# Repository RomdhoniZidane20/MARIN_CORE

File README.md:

# MARIN Core
ICHIRO Controller Manager Board for Dynamixel
## Features

* RS485/TTL on 4 Buses
* BNO055 IMU Sensor With Absolute Orientation
* Hot Swap switching System for Mini PC (Intel NUC 10th)
* Motor Voltage Power Switch System

## Include Hardware and Software setup for dxl_board

Documentations for [FT4232_dxl](https://github.com/RomdhoniZidane20/ichiro_dxl_board/tree/main/firmware/FT4232)

Documentations for [MARIN_CORE](https://github.com/RomdhoniZidane20/ichiro_dxl_board/tree/main/firmware/Marin_Core_Firmware)

Documentations for [Loadcel_dxl](https://github.com/RomdhoniZidane20/ichiro_dxl_board/tree/main/firmware/Loadcell)

Documentations for [Interface_dxl](https://github.com/RomdhoniZidane20/ichiro_dxl_board/tree/main/firmware/Interface)

## License 
The FT4232 and ADM3078E eagle library of this repository based on 
"SUSTAINA-OP" by [Masato Kubotera](https://github.com/MasatoKubotera) is licensed under [ CC BY-NC-SA 4.0](https://creativecommons.org/licenses/by-nc-sa/4.0/).

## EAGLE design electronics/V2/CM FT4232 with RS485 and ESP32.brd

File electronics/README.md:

# License 
The FT4232 and ADM3078E eagle library of this repository based on  
"SUSTAINA-OP" by [Masato Kubotera](https://github.com/MasatoKubotera) is licensed under [ CC BY-NC-SA 4.0](https://creativecommons.org/licenses/by-nc-sa/4.0/).

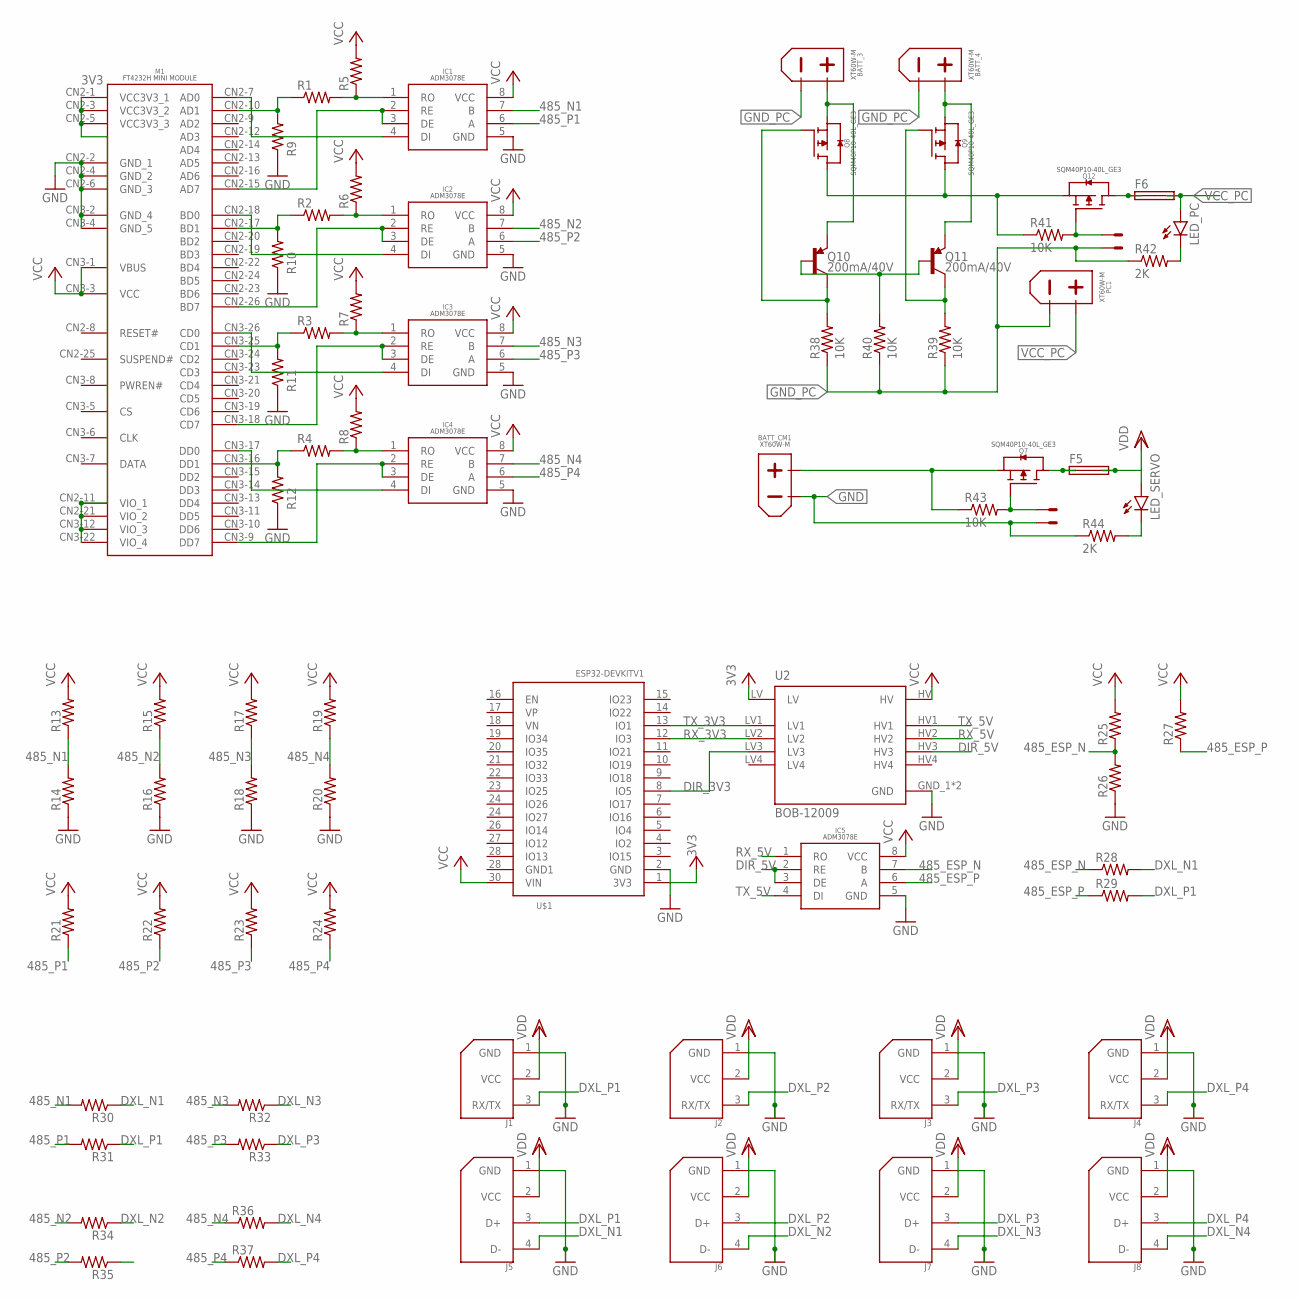
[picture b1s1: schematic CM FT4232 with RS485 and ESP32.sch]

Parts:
BATT_3, BATT_4: XT60PW-M
BATT_CM1: XT60PW-M
F5, F6: SHK20L
IC1, IC2, IC3, IC4, IC5: ADM3078E
J1, J2, J3, J4: 22-03-5035; 5267-3
J5, J6, J7, J8: 22-03-5045; 5267-4
LED_PC: LEDCHIPLED_0805; CHIPLED_0805
LED_SERVO: LEDCHIPLED_0805; CHIPLED_0805
M1: FT4232H_MINI_MODULE
PC1: XT60PW-M
Q7, Q8, Q9, Q12: SQM40P10-40L_GE3; TO-252-3
Q10, Q11: 200mA/40V; SOT23-3
R1, R2, R3, R4, R5, R6, R7, R8, R9, R10, R11, R12, R13, R14, R15, R16, R17, R18, R19, R20, R21, R22, R23, R24, R25, R26, R27, R28, R29, R30, R31, R32, R33, R34, R35, R36, R37: 0805
R38, R39, R40, R41, R43: 10K; M0805
R42, R44: 2K; M0805
U2: BOB-12009; CONV_BOB-12009
U$1: ESP32DEVKITV1; ESP32-DEVKITV1
X7, X8: 22-23-2021

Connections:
3V3: M1.CN2-1 (VCC3V3_1), M1.CN2-3 (VCC3V3_2), M1.CN2-5 (VCC3V3_3), M1.CN2-11 (VIO_1), M1.CN2-21 (VIO_2), M1.CN3-12 (VIO_3), M1.CN3-22 (VIO_4), U2.LV, U$1.1 (3V3)
485_ESP_N: IC5.7 (B), R25.1, R26.2, R28.1
485_ESP_P: IC5.6 (A), R27.1, R29.1
485_N1: IC1.7 (B), R13.1, R14.2, R30.2
485_N2: IC2.7 (B), R15.1, R16.2, R34.2
485_N3: IC3.7 (B), R17.1, R18.2, R32.2
485_N4: IC4.7 (B), R19.1, R20.2, R36.1
485_P1: IC1.6 (A), R21.1, R31.2
485_P2: IC2.6 (A), R22.1, R35.2
485_P3: IC3.6 (A), R23.1, R33.2
485_P4: IC4.6 (A), R24.1, R37.1
+2: BATT_CM1.+, Q7.3 (S), R43.1
+3: Q8.4 (D), Q9.4 (D), Q12.3 (S), R41.1
BLUE_LED: U$1.26 (IO14)
DI1: IC1.4 (DI), M1.CN2-7 (AD0)
DIR_3V3: U2.LV3, U$1.8 (IO5)
DIR_5V: IC5.2 (RE), IC5.3 (DE), U2.HV3
DRAIN2: F5.1A, F5.1B, Q7.4 (D)
DRAIN3: F6.1A, F6.1B, Q12.4 (D)
DXL_ENABLE: U$1.21 (IO32)
DXL_N1: J5.4 (D-), R28.2, R30.1
DXL_N2: J6.4 (D-), R34.1
DXL_N3: J7.4 (D-), R32.1
DXL_N4: J8.4 (D-), R36.2
DXL_P1: J1.3 (RX/TX), J5.3 (D+), R29.2, R31.1
DXL_P2: J2.3 (RX/TX), J6.3 (D+), R35.1
DXL_P3: J3.3 (RX/TX), J7.3 (D+), R33.1
DXL_P4: J4.3 (RX/TX), J8.3 (D+), R37.2
GND: BATT_CM1.1 (-), BATT_CM1.2 (-), BATT_CM1.-, IC1.5 (GND), IC2.5 (GND), IC3.5 (GND), IC4.5 (GND), IC5.5 (GND), J1.1 (GND), J2.1 (GND), J3.1 (GND), J4.1 (GND), J5.1 (GND), J6.1 (GND), J7.1 (GND), J8.1 (GND), M1.CN2-2 (GND_1), M1.CN2-4 (GND_2), M1.CN2-6 (GND_3), M1.CN3-2 (GND_4), M1.CN3-4 (GND_5), R9.1, R10.1, R11.1, R12.1, R14.1, R16.1, R18.1, R20.1, R26.1, R44.1, U2.GND_1 (GND), U2.GND_2 (GND), U$1.2 (GND), X7.2
GND_PC: BATT_3.1 (-), BATT_3.2 (-), BATT_3.-, BATT_4.1 (-), BATT_4.2 (-), BATT_4.-, PC1.1 (-), PC1.2 (-), PC1.-, R38.1, R39.1, R40.1, R42.1, X8.2
GREE_LED: U$1.28 (IO13)
unnamed: IC2.2 (RE), IC2.3 (DE), M1.CN2-26 (BD7)
unnamed: IC3.2 (RE), IC3.3 (DE), M1.CN3-18 (CD7)
unnamed: IC4.2 (RE), IC4.3 (DE), M1.CN3-9 (DD7)
unnamed: M1.CN2-10 (AD1), R1.1, R9.2
unnamed: M1.CN2-17 (BD1), R2.1, R10.2
unnamed: IC2.1 (RO), R2.2, R6.1
unnamed: IC3.1 (RO), R3.2, R7.1
unnamed: M1.CN3-25 (CD1), R3.1, R11.2
unnamed: M1.CN3-16 (DD1), R4.1, R12.2
unnamed: IC4.1 (RO), R4.2, R8.1
unnamed: IC2.4 (DI), M1.CN2-18 (BD0)
unnamed: IC3.4 (DI), M1.CN3-26 (CD0)
unnamed: IC4.4 (DI), M1.CN3-17 (DD0)
unnamed: BATT_3.+, Q8.3 (S), Q10.2 (E)
unnamed: BATT_4.+, Q9.3 (S), Q11.2 (E)
unnamed: Q8.1 (G), Q10.3 (C), R38.2
unnamed: Q9.1 (G), Q11.3 (C), R39.2
unnamed: Q10.1 (B), Q11.1 (B), R40.2
unnamed: Q12.1 (G), R41.2, X8.1
unnamed: Q7.1 (G), R43.2, X7.1
unnamed: LED_PC.C, R42.2
unnamed: LED_SERVO.C, R44.2
RE1: IC1.2 (RE), IC1.3 (DE), M1.CN2-15 (AD7)
RED_LED: U$1.27 (IO12)
RO1: IC1.1 (RO), R1.2, R5.1
RX_3V3: U2.LV2, U$1.12 (IO3)
RX_5V: IC5.1 (RO), U2.HV2
SCL: U$1.14 (IO22)
SDA: U$1.11 (IO21)
SW_START: U$1.19 (IO34)
SW_STOP: U$1.20 (IO35)
TX_3V3: U2.LV1, U$1.13 (IO1)
TX_5V: IC5.4 (DI), U2.HV1
VCC: IC1.8 (VCC), IC2.8 (VCC), IC3.8 (VCC), IC4.8 (VCC), IC5.8 (VCC), M1.CN3-1 (VBUS), M1.CN3-3 (VCC), R5.2, R6.2, R7.2, R8.2, R13.2, R15.2, R17.2, R19.2, R21.2, R22.2, R23.2, R24.2, R25.2, R27.2, U2.HV, U$1.30 (VIN)
VCC_PC: F6.2A, F6.2B, LED_PC.A, PC1.+
VDD: F5.2A, F5.2B, J1.2 (VCC), J2.2 (VCC), J3.2 (VCC), J4.2 (VCC), J5.2 (VCC), J6.2 (VCC), J7.2 (VCC), J8.2 (VCC), LED_SERVO.A

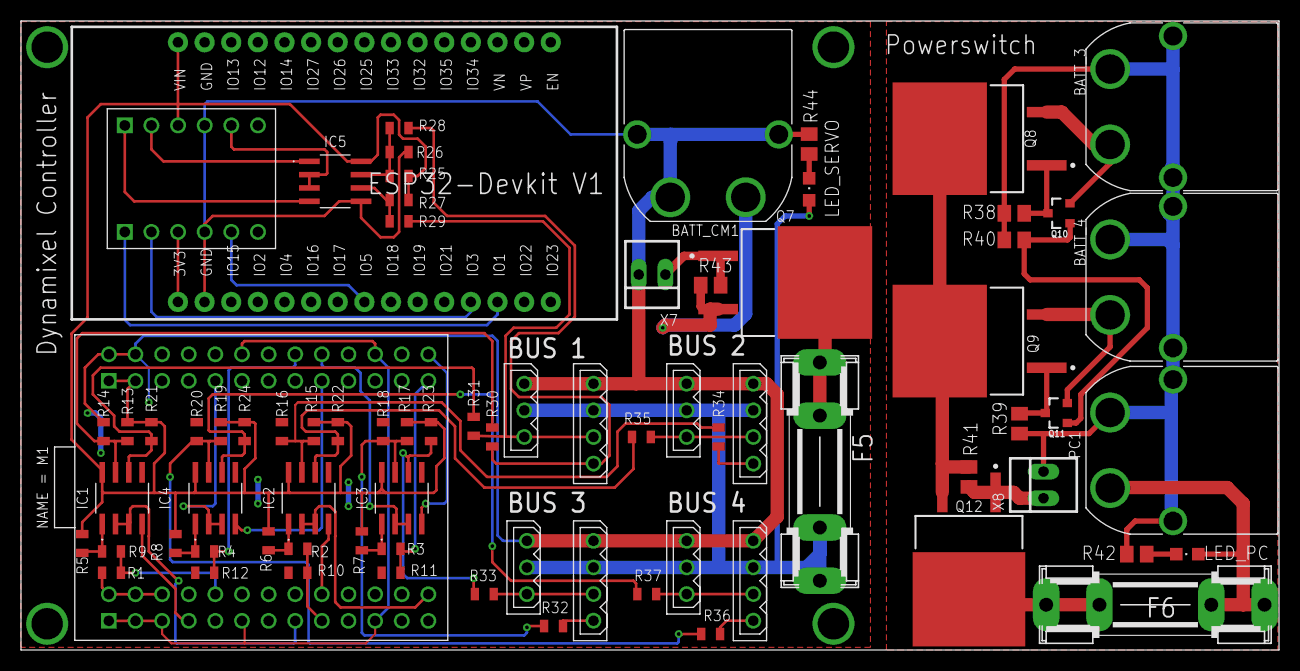
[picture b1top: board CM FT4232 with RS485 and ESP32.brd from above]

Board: 2 copper layers, 120.0 x 60.0 mm, 76 parts (0 on the bottom side), 59 nets.

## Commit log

2022-08-27 add framework
2022-08-27 change framework to firmware
2022-08-28 change readme
2022-08-28 little change on void setup and define var
2022-08-28 blocking fixing
2022-08-28 folder change
2022-08-28 fix issues
2022-08-28 fix overflow issues on IMU
2022-09-02 add sch, firmware add LED
2022-09-04 add FT4232 setup
2022-09-09 change data description
2022-09-09 data desc change
2022-09-10 sch and brd files revision
2022-09-12 delay bug fix
2022-09-19 Loadcell firmware
2022-09-19 add Interface firmware
2022-09-19 firmware add Interface
2022-09-21 add callback variables
2022-09-21 code clean
2022-09-22 upload new revision design
2022-10-06 add BOM files
2022-12-01 add slave feature upgrade bulkread
2022-12-01 add image
2022-12-01 Upadte README.md
2023-01-15 Major Address changes
2023-01-16 board testing
2023-01-17 minor change address
2023-01-24 insert array to dxl
2023-01-24 rearanged address list
2023-01-28 Add MARIN_CORE V4
2023-03-08 add feature reset chip_dxl and LED
2023-03-12 Update README.md
    ICHIRO Controller Manager Board for Dynamixel
2023-03-15 add accel gyro data and rearanged address
2023-03-16 bulkread address bug fixed
2023-03-27 Implement dual core on MARIN CORE ESP32
2023-03-27 Implement Dual Core Marin Core ESP32
2023-04-12 fix: Update Gyro and Accel data
2023-04-19 fix: read callback function
2023-05-02 add README.md (include CC BY-NC-SA 4.0 License)
2023-05-02 add CC BY-NC-SA 4.0 License Image
2023-05-02 push button swap pinout
2023-05-21 add executable file
2023-07-06 change data description for FT4232H
2023-07-06 firmware update
2023-08-07 add feature uart to marin core
2023-11-16 add schematic drawer names
2023-11-16 add drawer names

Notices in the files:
parts and their libraries:
SparkFun-DiscreteSemi: Licensing: Creative Commons ShareAlike 4.0 International - https://creativecommons.org/licenses/by-sa/4.0
